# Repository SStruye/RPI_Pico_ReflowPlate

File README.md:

# PICO Reflow Plate v1
PICO Reflow Plate is a diy reflow plate based around a raspberry PI pico. The user is capable of adjusting the settings of the reflow curve like, preheat temperature, soak time, reflow temperature en reflow time.
## Usage:
- After  turning on the power the start menu will appear on the screen. 
- Selecting the setup menu will take you to the different adjustable parameters.
- After adjusting the parameters go back to the start menu en press start reflow. This will start te process.
- The current temperature, elapsed time and current state will be displayed on the screen during the reflow process.
- After the reflowing is done, the plate will go in to cooldown mode until the plate is below 50 degrees.

## Build:
### Hardware:
As casing I repurposed an old broken DC power supply.

As plate I used an 1590BB hammond enclosure where I used aluminum tape to position the NTC sensors, thermal paste to asure good thermal transfer and high heat silicone to keep everything in place.

For ease of use, I made a pin distribution board for the PICO wich also holds the resistors for the led and the thermistors. The PCB was lasered on a fiber laser.

Furthermore a solidstate relay is used to control the PTC elements, a 230V to 3.3V buck converter is used to power the PICO and an LED is added indicating when the hotplate is too hot too touch.
As user interface a SSD1306 display and a KY-040 rotary encoder with push button is used.

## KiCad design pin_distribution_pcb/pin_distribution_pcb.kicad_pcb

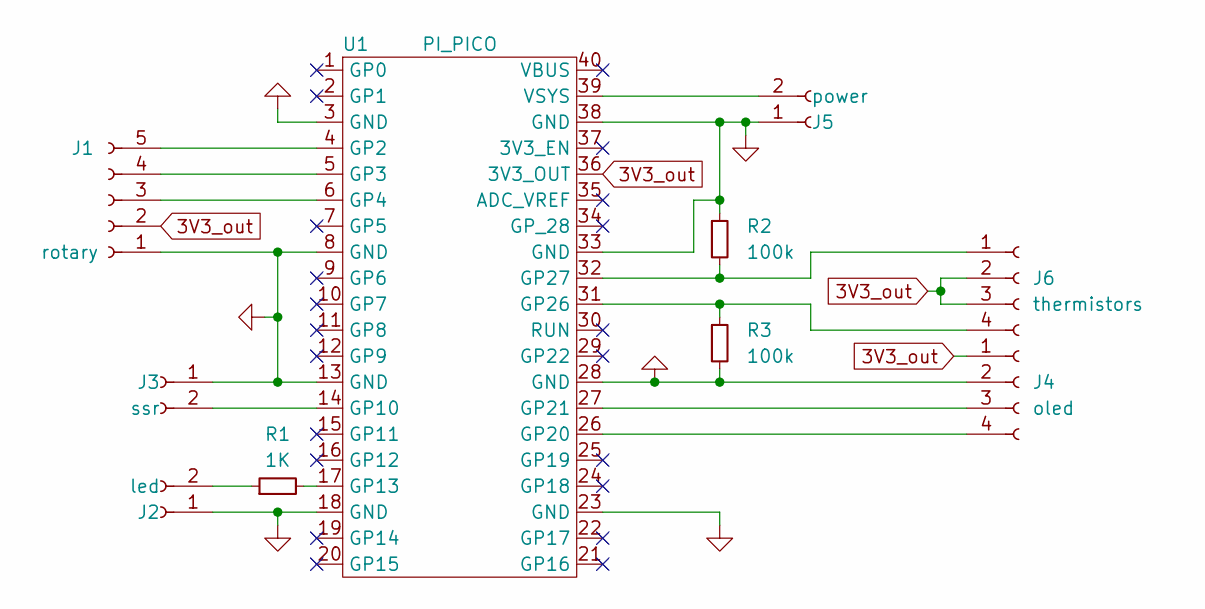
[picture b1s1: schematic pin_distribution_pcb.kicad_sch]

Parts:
J1: rotary; PinSocket_1x05_P2.54mm_Vertical
J2: led; PinSocket_1x02_P2.54mm_Vertical
J3: ssr; PinSocket_1x02_P2.54mm_Vertical
J4: oled; PinSocket_1x04_P2.54mm_Vertical
J5: power; PinSocket_1x02_P2.54mm_Vertical
J6: thermistors; PinSocket_1x04_P2.54mm_Vertical
R1: 1K; R_0805_2012Metric_Pad1.20x1.40mm_HandSolder
R2, R3: 100k; R_0805_2012Metric_Pad1.20x1.40mm_HandSolder
U1: PI_PICO

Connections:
3V3_out: J1.2, J4.1, J6.2, J6.3, U1.36 (3V3_OUT)
GND: J1.1, J2.1, J3.1, J4.2, J5.1, R2.1, R3.2, U1.3 (GND), U1.8 (GND), U1.13 (GND), U1.18 (GND), U1.23 (GND), U1.28 (GND), U1.33 (GND), U1.38 (GND)
unnamed: J5.2, U1.39 (VSYS)
unnamed: J6.1, R2.2, U1.32 (GP27)
unnamed: J6.4, R3.1, U1.31 (GP26)
unnamed: J2.2, R1.1
unnamed: R1.2, U1.17 (GP13)
unnamed: J1.5, U1.4 (GP2)
unnamed: J1.4, U1.5 (GP3)
unnamed: J1.3, U1.6 (GP4)
unnamed: J3.2, U1.14 (GP10)
unnamed: J4.4, U1.26 (GP20)
unnamed: J4.3, U1.27 (GP21)

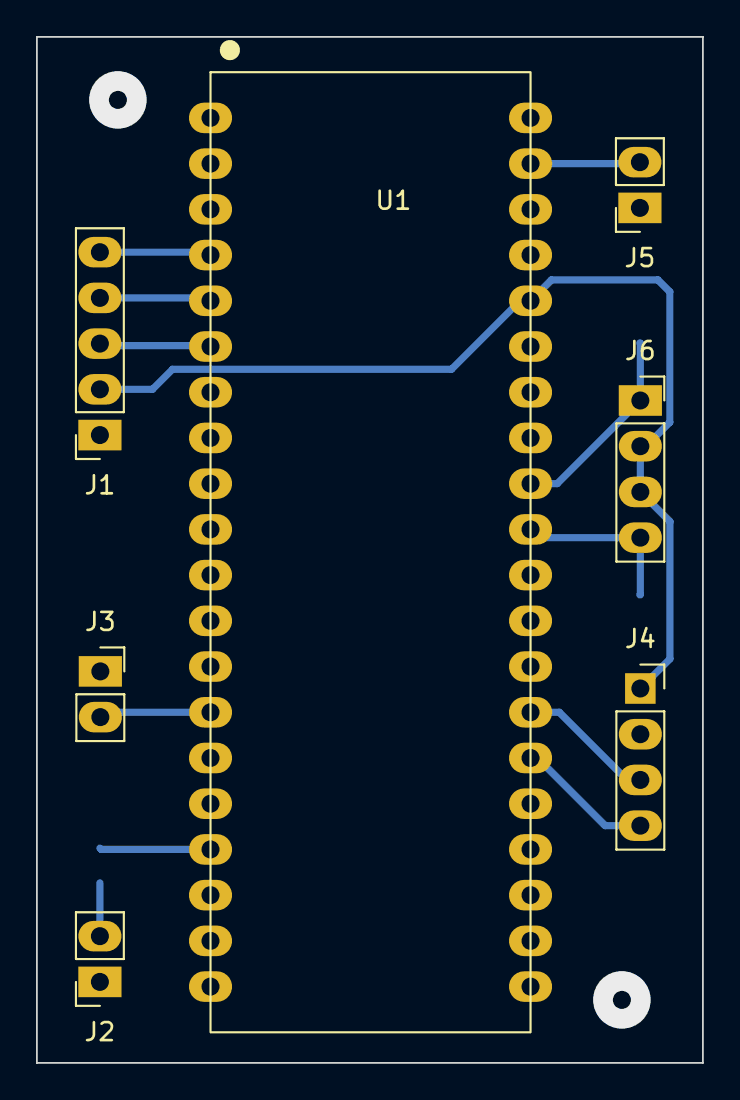
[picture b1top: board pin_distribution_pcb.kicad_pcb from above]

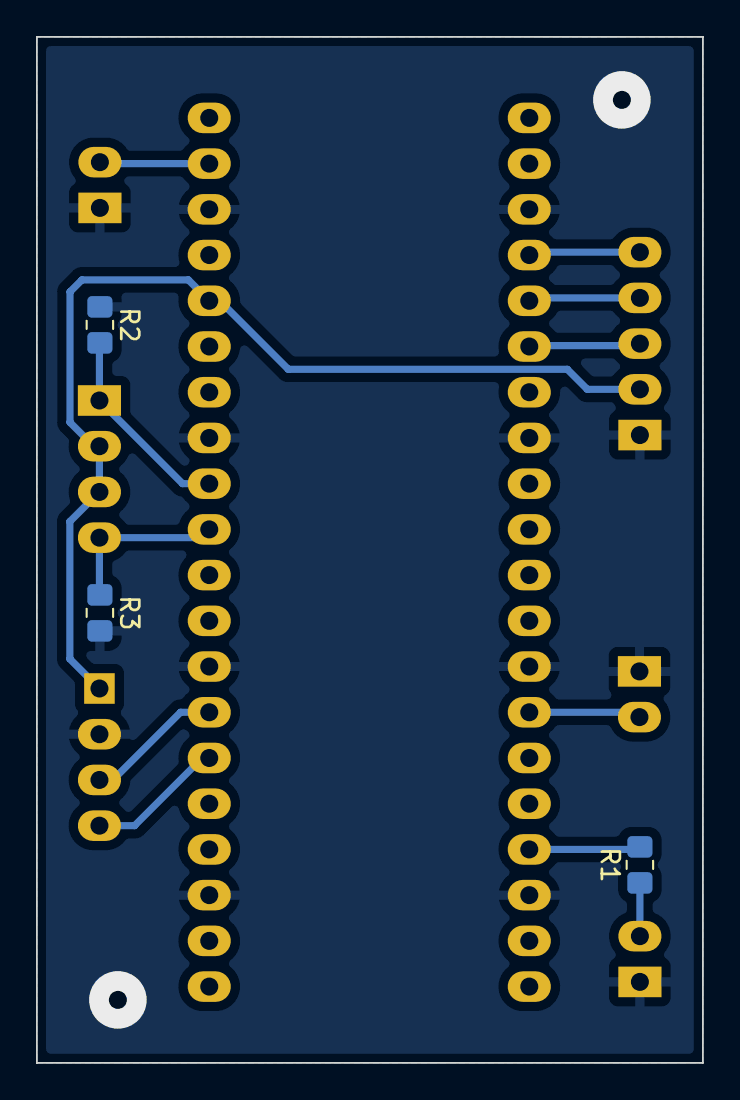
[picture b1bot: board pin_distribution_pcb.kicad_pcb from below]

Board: 2 copper layers, 37.0 x 57.0 mm, 10 parts (3 on the bottom side), 13 nets.

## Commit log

2022-11-21 add gitignore + dist pcb file dump
    added gitignore for kicad files + file dump from distribution pcb design
2022-11-21 pic dump
2022-11-21 add pic
2022-11-21 resize img
2022-11-28 code dump + flowchart
